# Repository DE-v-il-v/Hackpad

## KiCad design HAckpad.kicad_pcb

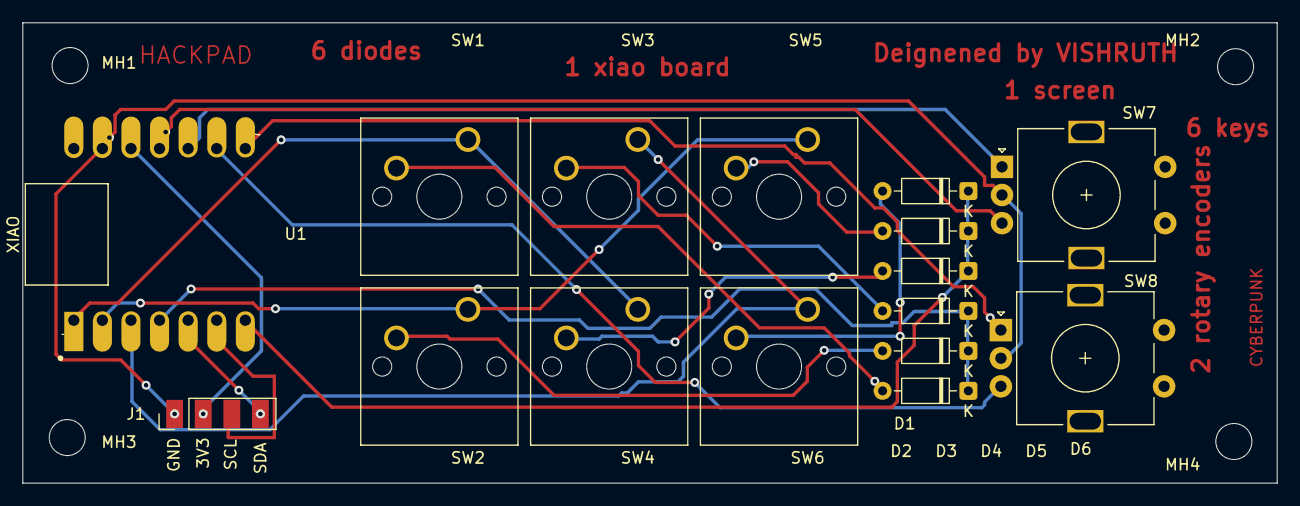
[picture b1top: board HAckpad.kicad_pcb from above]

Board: 2 copper layers, 111.5 x 40.9 mm, 20 parts (0 on the bottom side), 19 nets.

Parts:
D1, D2, D3, D4, D5, D6: 1N4148; D_DO-35_SOD27_P7.62mm_Horizontal
J1: Conn_01x04; PinHeader_1x04_P2.54mm_Vertical
MH1, MH2, MH3, MH4: MountingHole_3.2mm_M3
SW1, SW2, SW3, SW4, SW5, SW6: SW_Push; SW_Cherry_MX_1.00u_PCB
SW7, SW8: RotaryEncoder_Switch; RotaryEncoder_Alps_EC11E-Switch_Vertical_H20mm
U1: MOUDLE-SEEEDUINO-XIAO; XIAO-Generic-Hybrid-14P-2.54-21X17.8MM

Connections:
+3V3: J1.2, U1.12 (3V3)
/D4: J1.4, U1.5 (PA8_A4_D4_SDA)
/D5: J1.3, U1.6 (PA9_A5_D5_SCL)
/col1: SW1.1, SW4.1, U1.1 (PA02_A0_D0)
/col2: SW2.1, SW5.1, U1.2 (PA4_A1_D1)
/col3: SW3.1, SW6.1, U1.3 (PA10_A2_D2)
/e_1: SW8.A, U1.8 (PB09_A7_D7_RX)
/e_2: SW8.B, U1.9 (PA7_A8_D8_SCK)
/e_3: SW7.A, U1.10 (PA5_A9_D9_MISO)
/e_4: SW7.B, U1.11 (PA6_A10_D10_MOSI)
/row 1: D1.1 (K), D2.1 (K), D3.1 (K), U1.4 (PA11_A3_D3)
/row 2: D4.1 (K), D5.1 (K), D6.1 (K), U1.7 (PB08_A6_D6_TX)
GND: J1.1, SW7.C, SW8.C, U1.13 (GND)
unnamed: D1.2 (A), SW1.2
unnamed: D2.2 (A), SW2.2
unnamed: D3.2 (A), SW3.2
unnamed: D4.2 (A), SW4.2
unnamed: D5.2 (A), SW5.2
unnamed: D6.2 (A), SW6.2
